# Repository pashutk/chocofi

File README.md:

# chocofi

Keyboard shield and 3d printed case to use with Arduino ProMicro-like contoller.

- Split keyboard with 3 rows, 5 columns, and 3 thumbs per half
- Increased pinky column stagger
- Inspired by [Fifi keyboard](https://github.com/raychengy/fifi_split_keeb)
- Double-sided pcb (pcb can be used as left or right half)
- Pro Micro compatible footprint
- Easy to print, FDM-friendly two-piece case

## Artifacts

Gerbers are here: [pcb](/pcb/gerber.zip) and [top plate](/pcb/gerber-plate.zip)

Stls are here: [case folder](/case)

For more photos check out the [images folder](/images)

## By the way

Recommended batteries:

- [Nice nano docs](https://nicekeyboards.com/docs/nice-nano/#recommended-batteries-and-sockets) explains some basics
- [nRFmicro wiki](https://github.com/joric/nrfmicro/wiki/Batteries#301230) contains links to Aliexpress

Awesome libs used:

- [kbd.pretty](https://github.com/foostan/kbd) by foostan
- [keyswitches.pretty](https://github.com/daprice/keyswitches.pretty) by daprice

Also closest alternatives are:

- [raychengy/fifi](https://github.com/raychengy/fifi_split_keeb): non choc (mx switches)
- [davidphilipbarr/chocorne](https://github.com/davidphilipbarr/36keys/tree/master/42Keys/chocorne): non hotswap but choc-spaced corne (you can break off one column so it will be 5x3, but with corne pinky stagger)

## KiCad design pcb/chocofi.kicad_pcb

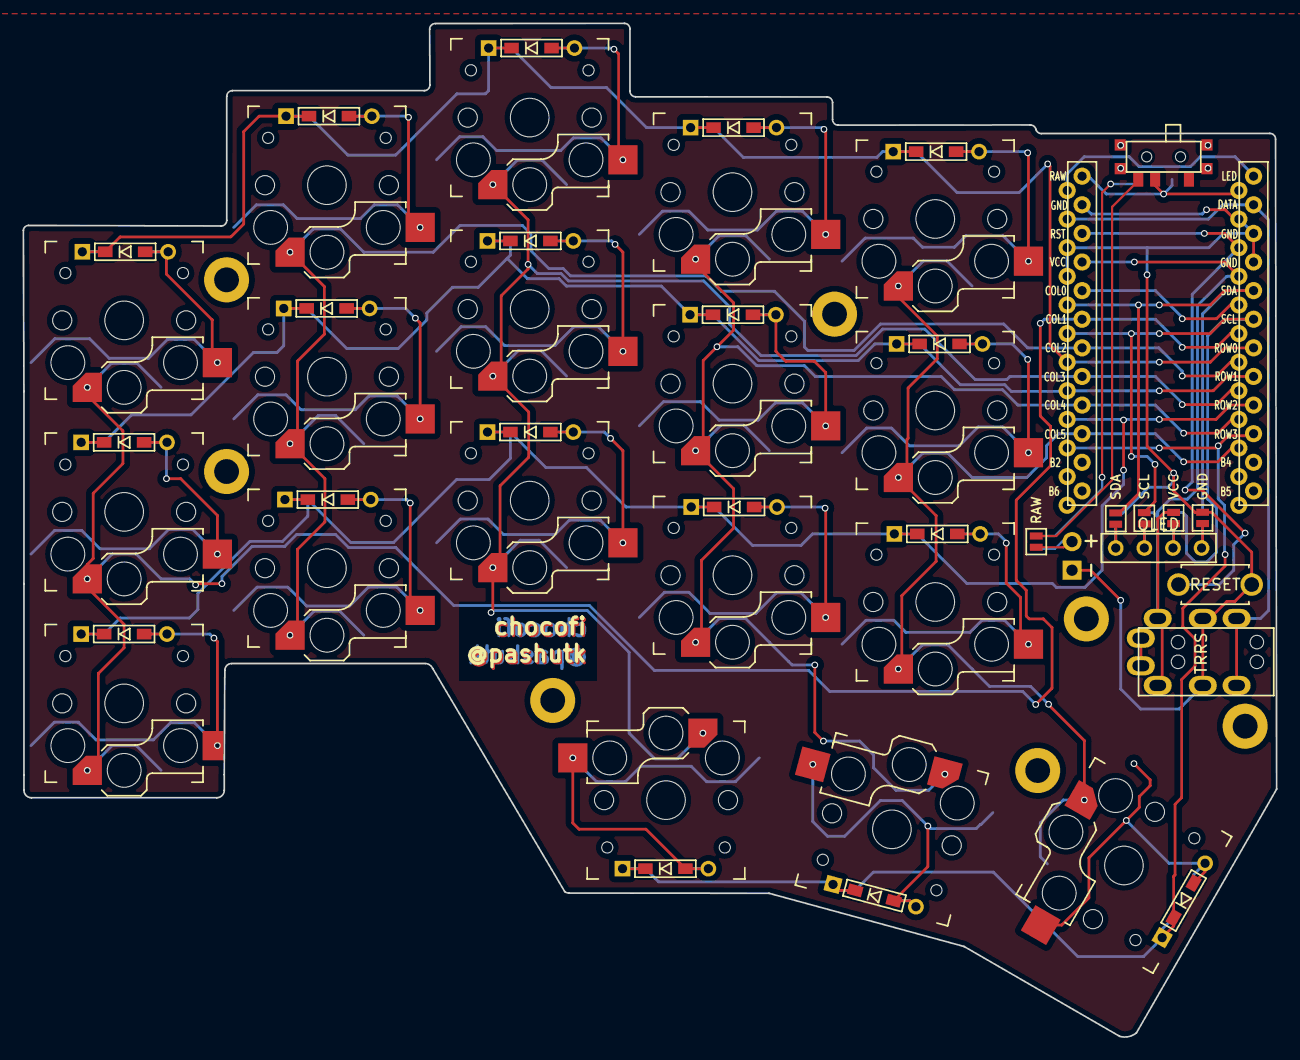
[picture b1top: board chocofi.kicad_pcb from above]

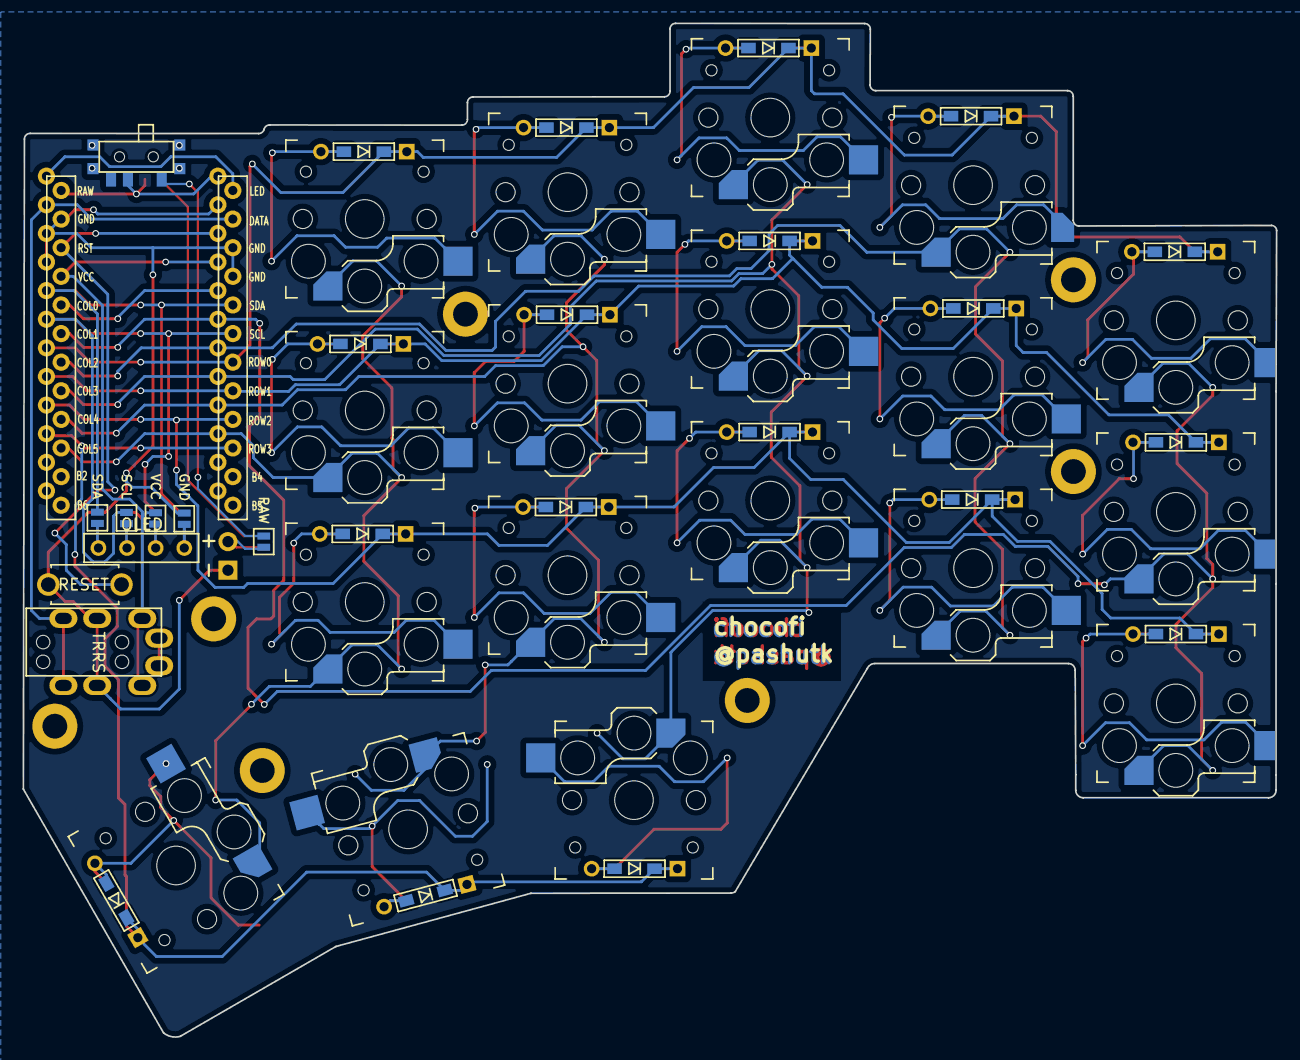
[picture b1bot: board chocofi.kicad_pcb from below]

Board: 2 copper layers, 111.3 x 90.0 mm, 60 parts (6 on the bottom side), 40 nets.

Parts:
D2, D3, D4, D5, D6, D8, D9, D10, D11, D12, D14, D15, D16, D17, D18, D19, D20, D21: D; D3_TH_SMD
H1: h1; LEGO_HOLE
J1: MJ-4PP-9
J2: OLED
J3: Conn_01x02_Female; Battery_TH
JP6, JP61: SDA; Jumper
JP61#2, JP62#2: RAW; Jumper
JP62, JP68: GND; Jumper
JP63, JP66: SCL; Jumper
JP64, JP65: VCC; Jumper
RSW1: Val**; ResetSW
SW1, SW2#2: SW_SPDT; SW_SPDT+H-MSK12C01_hor(7pin_SMD)
SW2, SW3, SW4, SW5, SW6, SW8, SW9, SW10, SW11, SW12, SW14, SW15, SW16, SW17, SW18, SW19, SW20, SW21: SW_PUSH; Kailh_socket_PG1350_reversible
U1: ProMicro; ProMicro_v2
h2: h2; LEGO_HOLE
h3: h3; LEGO_HOLE
h4: h4; LEGO_HOLE
h5: h5; LEGO_HOLE
h6: h6; LEGO_HOLE
h7: h7; LEGO_HOLE

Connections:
BAT_PLUS: J3.2, JP61#2.2, JP62#2.2
GND: J1.C, J3.1, JP62.1, JP68.1, RSW1.1, U1.3, U1.4, U1.23
unnamed: D2.2, SW2.2
unnamed: D3.2, SW3.2
unnamed: D4.2, SW4.2
unnamed: D5.2, SW5.2
unnamed: D6.2, SW6.2
unnamed: D8.2, SW8.2
unnamed: D9.2, SW9.2
unnamed: D10.2, SW10.2
unnamed: D11.2, SW11.2
unnamed: D12.2, SW12.2
unnamed: D14.2, SW14.2
unnamed: D15.2, SW15.2
unnamed: D16.2, SW16.2
unnamed: D17.2, SW17.2
unnamed: D18.2, SW18.2
unnamed: D19.2, SW19.2
unnamed: D20.2, SW20.2
unnamed: D21.2, SW21.2
unnamed: J2.3, JP65.2, JP66.2
unnamed: J2.4, JP6.2, JP68.2
unnamed: J2.2, JP63.2, JP64.2
unnamed: J2.1, JP61.2, JP62.2
unnamed: SW1.2 (B), SW2#2.2 (B), U1.24
SCL: JP63.1, JP66.1, U1.6
SDA: JP6.1, JP61.1, U1.5
SW_RAW_2: JP61#2.1, SW1.3 (C)
VCC: J1.D, JP64.1, JP65.1, U1.21
col1: SW2.1, SW8.1, SW14.1, U1.19
col2: SW3.1, SW9.1, SW15.1, U1.18
col3: SW4.1, SW10.1, SW16.1, SW19.1, U1.17
col4: SW5.1, SW11.1, SW17.1, SW20.1, U1.16
col5: SW6.1, SW12.1, SW18.1, SW21.1, U1.15
data: J1.B, U1.2
reset: RSW1.2, U1.22
row0: D2.1, D3.1, D4.1, D5.1, D6.1, U1.7
row1: D8.1, D9.1, D10.1, D11.1, D12.1, U1.8
row2: D14.1, D15.1, D16.1, D17.1, D18.1, U1.9
row3: D19.1, D20.1, D21.1, U1.10

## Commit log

2021-08-29 Fix refs
2021-08-29 add top plate
2021-10-10 Remove excessive corner pad surface, rm doorka logo
2021-10-10 Mv everything to pcb folder
2021-10-10 Add images and readme
2021-10-10 Regenerate gerber files
2021-10-10 Compress new gerbers
2021-10-10 Add case
2021-10-10 Crop main image
2021-10-10 Fix readme
2021-12-22 Light-weight chocofi (Easy build with a simple PCB) (without hotswap).
2021-12-24 Added footprints
2021-12-26 Removed selection of landing zones of switches and their names. Added generated gerber
2021-12-27 Removed landing zones and their names
2021-12-27 Removed G** from footprints
2021-12-27 Generate gerber files
2021-12-30 Removed holes in keyswitches.pretty - SW_PG1350_reversible.kicad_mod
2021-12-30 Generated correct gerber file
2022-01-04 change
2022-01-10 Add 13.9x13.9mm switch cutouts top case, add step files
2022-01-18 Pcb: add corne-light-rescue
2022-01-23 Add power switch. Broken nets on scheme.
2022-04-05 Add CERN OHL P license
2022-09-29 Use thicker power trace
2022-11-24 Add recommended batteries to README.md
    #13
